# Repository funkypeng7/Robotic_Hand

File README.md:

##### Robotic Hand
Find all required files in the relevant folders

##### How to compile code
Open one of the `.ido` files in the Ardinuo IDE, that will open all the other ones as tabs

##### How to 3D print
I used a Prusa i3 Mk2, with these settings
- 0.15mm layer height
- 25% infill

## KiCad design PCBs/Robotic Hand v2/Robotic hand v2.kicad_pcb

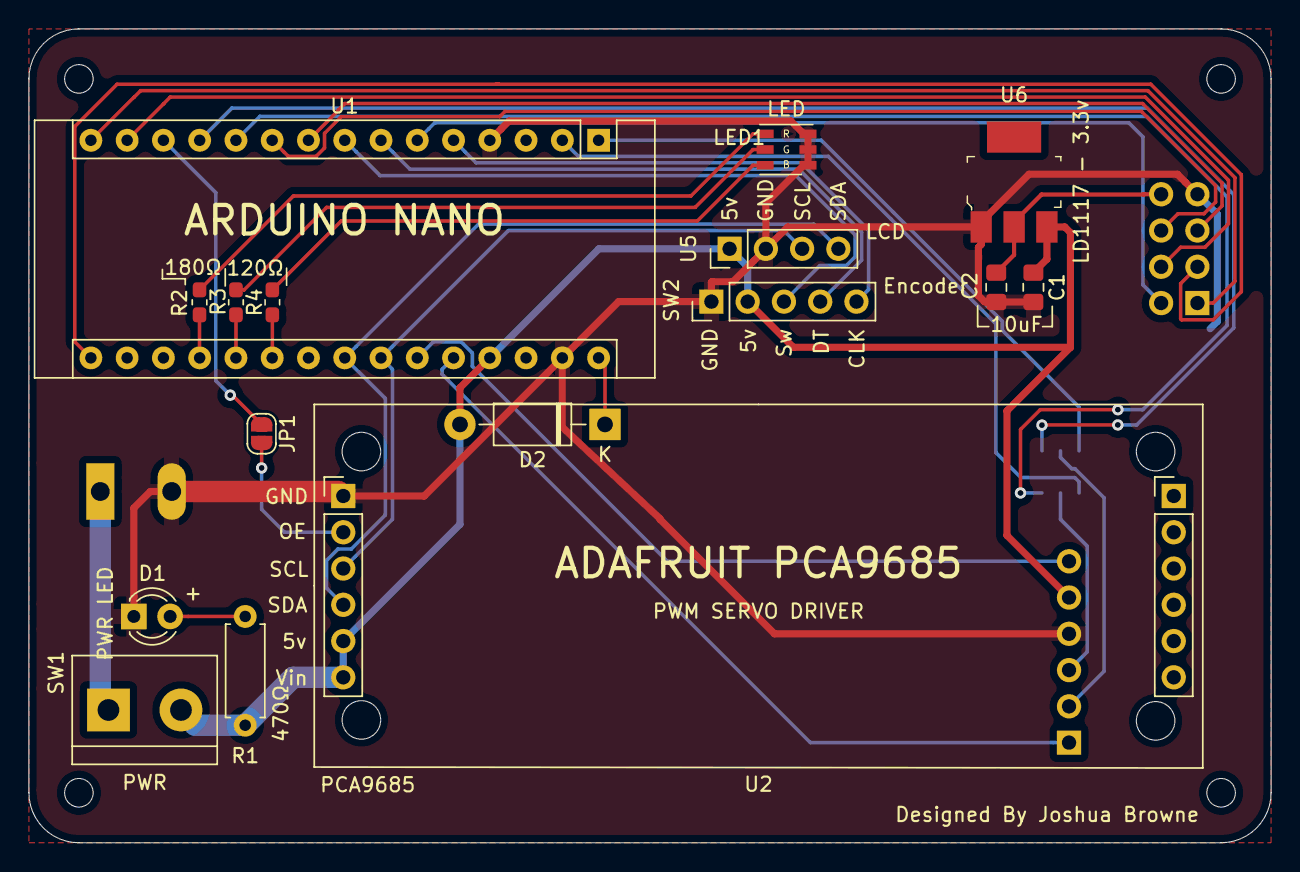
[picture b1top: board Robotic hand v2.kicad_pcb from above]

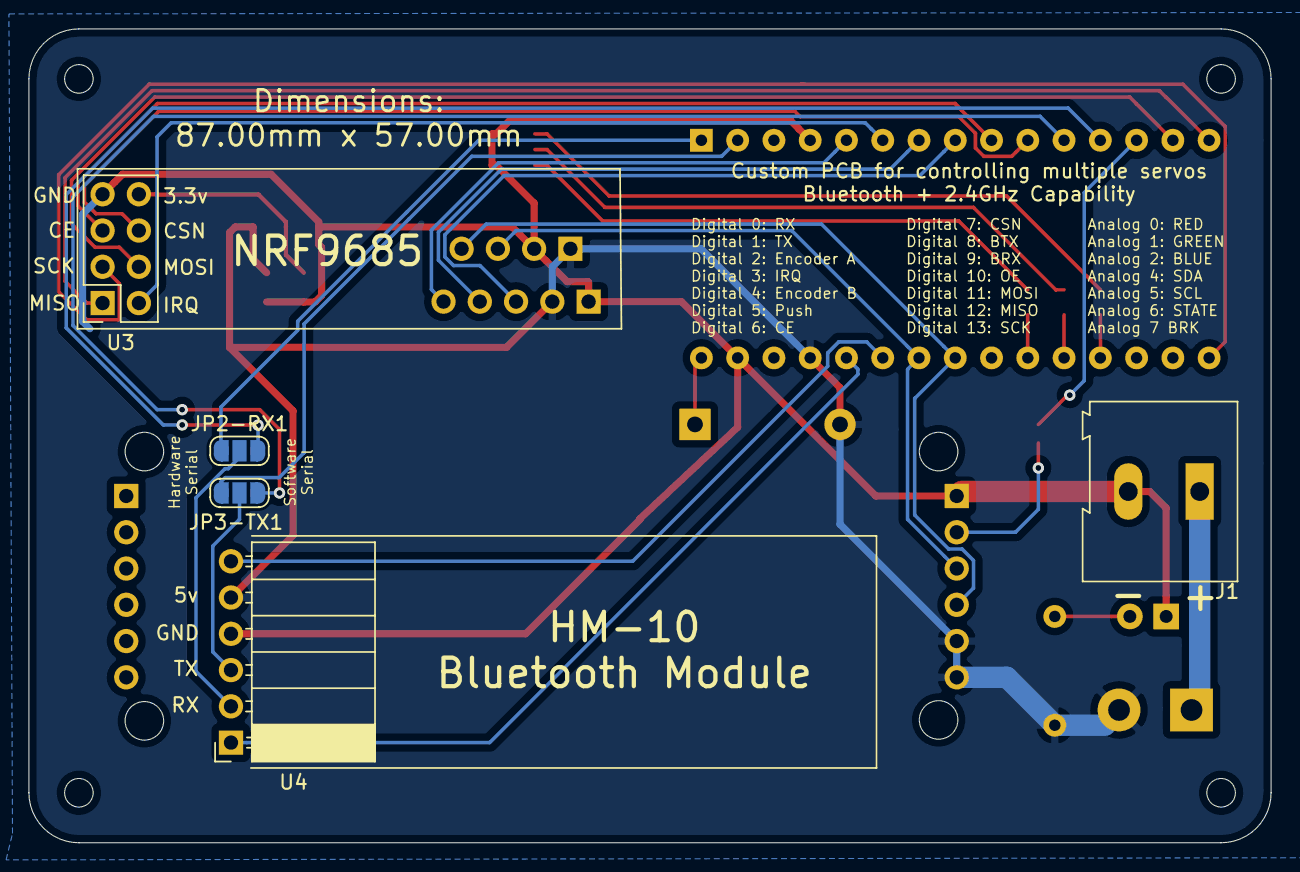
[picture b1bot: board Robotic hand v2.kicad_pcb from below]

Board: 2 copper layers, 87.0 x 57.0 mm, 21 parts (5 on the bottom side), 33 nets.

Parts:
C1, C2: 10uF; C_0805_2012Metric_Pad1.15x1.40mm_HandSolder
D1: PWR LED; LED_D3.0mm
D2: D; D_DO-41_SOD81_P10.16mm_Horizontal
J1: Barrel_Jack; TerminalBlock_Altech_AK300-2_P5.00mm
JP1: Enable OE; SolderJumper-2_P1.3mm_Open_RoundedPad1.0x1.5mm
JP2-RX1: Rx; SolderJumper-3_P1.3mm_Open_RoundedPad1.0x1.5mm
JP3-TX1: Tx; SolderJumper-3_P1.3mm_Open_RoundedPad1.0x1.5mm
LED1: LED_RGB; RGB LED
R1: 470Ω; R_Axial_DIN0207_L6.3mm_D2.5mm_P7.62mm_Horizontal
R2: 180Ω; R_0603_1608Metric_Pad1.05x0.95mm_HandSolder
R3, R4: 120Ω; R_0603_1608Metric_Pad1.05x0.95mm_HandSolder
SW1: PWR; TerminalBlock_bornier-2_P5.08mm
SW2: Rotary_Encoder_Switch; PinHeader_1x05_P2.54mm_Vertical
U1: Arduino_Nano_v3.x; Arduino_Nano
U2: PCA9685
U3: Nrf24l01; PinSocket_2x04_P2.54mm_Vertical
U4: HM-10
U5: I2C LCD; PinHeader_1x04_P2.54mm_Vertical
U6: LD1117 - 3.3v; SOT-223

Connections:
/3v3: C2.1, U3.2, U6.2
/5v: C1.1, D2.2, R1.2, SW1.2, SW2.2, U1.27, U2.5, U2.6, U4.2, U5.1, U6.3
/BRX: JP2-RX1.1, U1.12
/BTX: JP3-TX1.1, U1.11
/Blue: R4.2, U1.21
/Brk: U1.26, U4.6
/CE: U1.9, U3.3
/CSN: U1.10, U3.4
/EncoderA: SW2.1, U1.5
/EncoderB: SW2.3, U1.7
/Green: R3.2, U1.20
/IRQ: U1.6, U3.8
/MISO: U1.15, U3.7
/MOSI: U1.14, U3.6
/OE: JP1.1, U1.13
/Red: R2.2, U1.19
/Rx: JP2-RX1.3, U1.1
/SCK: U1.16, U3.5
/SCL: U1.24, U2.3, U5.3
/SDA: U1.23, U2.4, U5.4
/State: U1.25, U4.1
/Sw: SW2.4, U1.8
/Tx: JP3-TX1.3, U1.2
GND: C1.2, C2.2, D1.1, J1.2, LED1.1, LED1.2, LED1.3, SW2.5, U1.4, U1.29, U2.1, U3.1, U4.3, U5.2, U6.1
unnamed: D1.2, R1.1
unnamed: D2.1, U1.30
unnamed: J1.1, SW1.1
unnamed: JP1.2, U2.2
unnamed: JP2-RX1.2, U4.5
unnamed: JP3-TX1.2, U4.4
unnamed: LED1.4, R2.1
unnamed: LED1.5, R3.1
unnamed: LED1.6, R4.1

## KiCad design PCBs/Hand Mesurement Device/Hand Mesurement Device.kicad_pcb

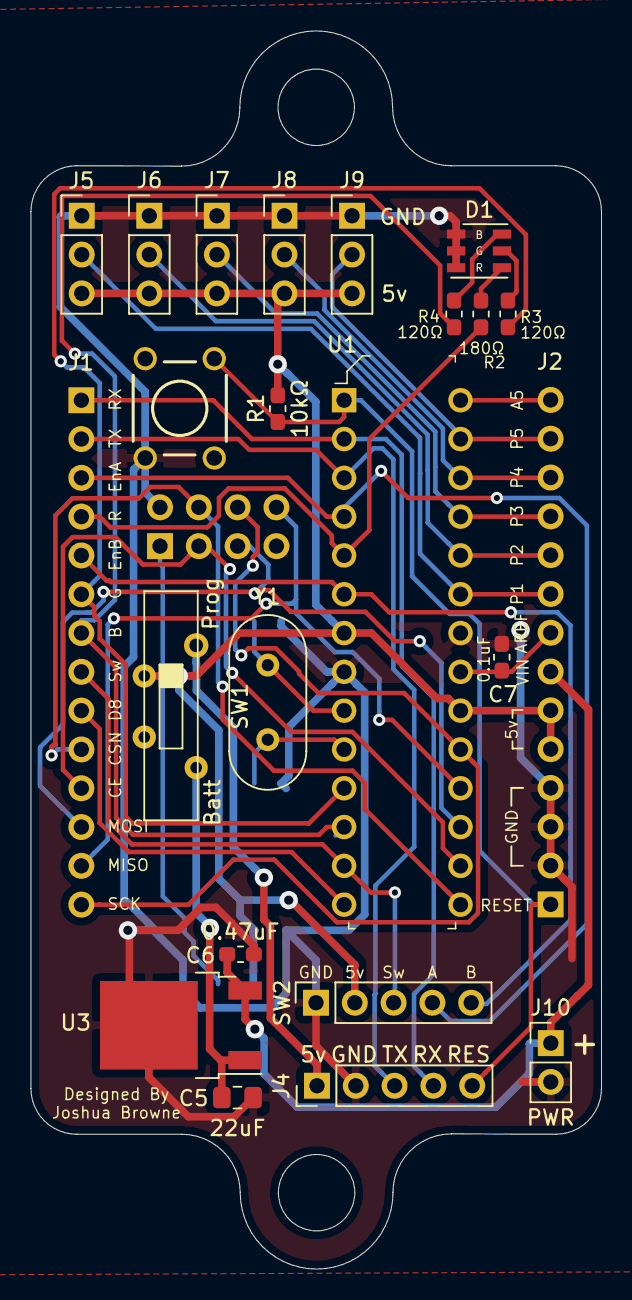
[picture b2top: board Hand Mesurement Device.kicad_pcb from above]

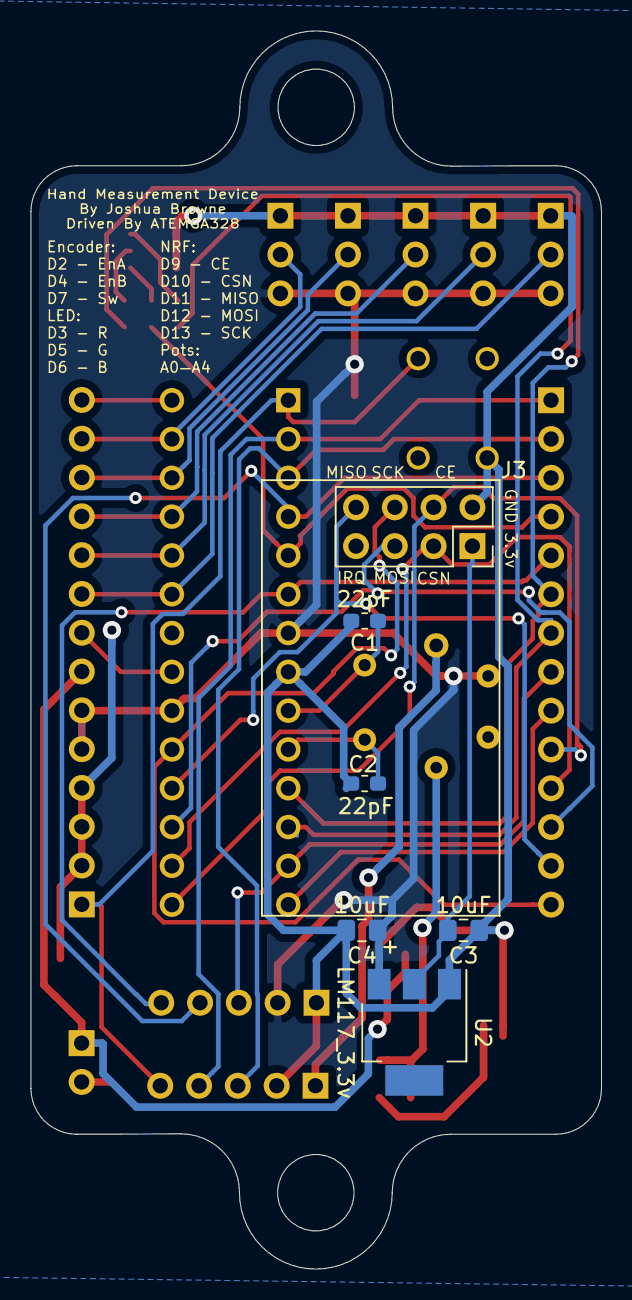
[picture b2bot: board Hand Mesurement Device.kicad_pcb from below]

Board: 2 copper layers, 37.4 x 81.0 mm, 29 parts (6 on the bottom side), 33 nets.

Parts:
C1, C2: 22pF; C_0603_1608Metric_Pad1.05x0.95mm_HandSolder
C3, C4: 10uF; C_0805_2012Metric_Pad1.15x1.40mm_HandSolder
C5: 22uF; C_0805_2012Metric_Pad1.15x1.40mm_HandSolder
C6: 0.47uF; C_0603_1608Metric_Pad1.05x0.95mm_HandSolder
C7: 0.1uF; C_0603_1608Metric_Pad1.05x0.95mm_HandSolder
D1: LED_RGB; RGB LED
J1: Rail 1; PinHeader_1x14_P2.54mm_Vertical
J2: Rail 2; PinHeader_1x14_P2.54mm_Vertical
J3: NRF24l01
J4: Programming; PinHeader_1x05_P2.54mm_Vertical
J5, J6, J7, J8, J9: Conn_01x03; PinHeader_1x03_P2.54mm_Vertical
J10: PWR; PinHeader_1x02_P2.54mm_Vertical
R1: 10kΩ; R_0603_1608Metric_Pad1.05x0.95mm_HandSolder
R2: 180Ω; R_0603_1608Metric_Pad1.05x0.95mm_HandSolder
R3, R4: 120Ω; R_0603_1608Metric_Pad1.05x0.95mm_HandSolder
S1: KS-01Q-01_Obsolete; SW_PUSHBUTTON_PTH
SW1: SW_SP3T; Sp3t K3-1336D-K1
SW2: Rotary_Encoder_Switch; RotaryEncoderSocket
U1: ATMEGA328-PU; DIP-28_W7.62mm
U2: LM117_3.3v; SOT-223
U3: L7805_5v; TO-252-2
Y1: Crystal; Crystal_HC49-4H_Vertical

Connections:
/3v3: C3.2, J3.2, U2.2
/5v: C4.1, J2.5, J2.6, J5.3, J6.3, J7.3, J8.3, J9.3, R1.2, SW1.2, SW2.2, U1.7, U1.20, U2.3
/5vPinIn: J4.1, SW1.1
/5vRegOut: C5.2, SW1.4, U3.1
/A0: J2.9, J5.2, U1.23
/A1: J2.10, J6.2, U1.24
/A2: J2.11, J7.2, U1.25
/A3: J2.12, J8.2, U1.26
/A4: J2.13, J9.2, U1.27
/A5: J2.14, U1.28
/AREF: C7.1, J2.8, U1.21
/CE: J1.10, J3.3, U1.15
/CSN: J1.11, J3.4, U1.16
/D2: J1.3, SW2.1, U1.4
/D3: J1.4, R2.2, U1.5
/D4: J1.5, SW2.3, U1.6
/D5: J1.6, R3.2, U1.11
/D6: J1.7, R4.2, U1.12
/D7: J1.8, SW2.4, U1.13
/D8: J1.9, U1.14
/D11: J1.12, J3.6, U1.17
/D12: J1.13, J3.7, U1.18
/D13: J1.14, J3.5, U1.19
/RESET: J2.1, J4.5, R1.1, S1.1, U1.1
/RX: J1.1, J4.4, U1.2
/TX: J1.2, J4.3, U1.3
/VIN: C6.2, J2.7, J10.1, U3.3
GND: C1.2, C2.2, C3.1, C4.2, C5.1, C6.1, C7.2, D1.1, D1.2, D1.3, J2.2, J2.3, J2.4, J3.1, J4.2, J5.1, J6.1, J7.1, J8.1, J9.1, J10.2, S1.4, SW2.5, U1.8, U1.22, U2.1, U3.2
unnamed: C1.1, U1.9, Y1.2
unnamed: C2.1, U1.10, Y1.1
unnamed: D1.4, R2.1
unnamed: D1.5, R3.1
unnamed: D1.6, R4.1

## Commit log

2020-08-16 Started Github
2020-08-18 Added Basic UI
2020-08-19 UI Rework in progress
2020-08-19 Listed UI
2020-08-20 Finger Data Section
2020-08-21 + reverse and reworked finger data
2020-09-05 Semi Working
2020-09-09 UI Code Refactor
2020-09-12 Config rework
2020-09-14 Method Renames
2020-09-16 UI Second Refactor
2020-09-16 PROGMEM migration in progress
2020-09-17 All UI Strings stored in PROGMEM
2020-11-01 All File Linked
2020-11-10 File Reorganisation
